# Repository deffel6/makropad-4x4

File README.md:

# Makropad 4 × 4

16 Tasten im 19,05-mm-Raster, Cherry MX, gesteuert von einem Pro Micro über
acht Lötpunkte. Platine **96,2 × 92,2 mm**, zwei Lagen, vollständig verdrahtet.

Entwurf, Fertigungsdaten und Firmware liegen hier zusammen. Die Platine ist
nicht von Hand gezeichnet, sondern wird aus einem Skript erzeugt — Rastermaß
und Tastenzahl sind dadurch eine Zahl im Kopf der Datei.

## Anschlüsse

Acht durchkontaktierte Lötpunkte in einer Reihe am oberen Rand, im
2,54-mm-Raster. Von links:

```
R3  R2  R1  R0  C0  C1  C2  C3
```

| Lötpunkt | QMK | Aufdruck am Pro Micro | Arduino |
|---|---|---|---|
| `R0` | `D4` | 4 | 4 |
| `R1` | `C6` | 5 | 5 |
| `R2` | `D7` | 6 | 6 |
| `R3` | `E6` | 7 | 7 |
| `C0` | `F4` | A3 | 21 |
| `C1` | `F5` | A2 | 20 |
| `C2` | `F6` | A1 | 19 |
| `C3` | `F7` | A0 | 18 |

Zeilen auf der linken Stiftleiste, Spalten auf der rechten, beide in der
unteren Hälfte des Moduls — so bleiben die Drähte kurz.

**Frei bleiben** `D0`/`D1` (I²C, für ein Display), `D2`/`D3` (seriell),
`B1`/`B2`/`B3` (SPI) sowie `B4`/`B5`/`B6`. Versorgung braucht die Platine
keine: Eine Tastenmatrix wird allein über die acht Signalleitungen abgefragt.

## Verdrahtung

```
Spalte ──── Schalter ──── Diode ──►── Zeile
                          Anode   Kathode
```

Die Diode verhindert Phantomtasten: Ohne sie schließen drei gleichzeitig
gedrückte Tasten einen Pfad über eine vierte, die gar nicht gedrückt ist.
Stromrichtung Spalte → Zeile, in QMK `COL2ROW`.

Spalten laufen senkrecht auf der Vorderseite, Zeilen waagerecht auf der
Rückseite. Weil jeder Lötpunkt auf der Achse seiner Bahn sitzt, kreuzt sich
nichts — die Platine kommt ohne eine einzige Durchkontaktierung aus.

| Vorderseite | Rückseite |
|---|---|
|  |  |

## Fertigen lassen

`hardware/keypad4x4-gerber.zip` bei einem Hersteller hochladen, nicht
entpacken. Voreinstellungen passen: zweilagig, 1,6 mm, HASL.

Geprüft ist die Platine mit dem Regelprüfer von KiCad 10:

```
Regelverstöße:        0
Unverbundene Stellen: 0
```

Dazu gegengelesen: Jedes der 40 Lötaugen hat eine durchkontaktierte Bohrung,
alle 52 Löcher ohne Kupfer sind vorhanden, 92 Bohrungen gesamt. Das Rastermaß
beträgt überall exakt 19,05 mm — auch von Zapfenloch zu Zapfenloch.

Wer die Dioden bestücken lassen will, findet in `bestueckung/` die Stückliste
und die Positionsdatei. Die 16 SOD-123 sitzen auf der **Unterseite**.

## Stückliste

| Menge | Teil | Hinweis |
|---|---|---|
| 16 | Cherry MX oder kompatibel | **PCB-Bauform mit fünf Beinen** |
| 16 | 1N4148W, SOD-123 | Rückseite, SMD |
| 1 | Pro Micro ATmega32U4 | oder steckkompatibler Ersatz |
| 1 | Stiftleiste 8-polig, 2,54 mm | |
| 4 | M2-Schraube mit Abstandshalter | Löcher Ø 2,2 mm |

Die Schalter brauchen die PCB-montierte Bauform mit zwei Kunststoffzapfen
neben den Kontakten — die Platine hat Löcher dafür. Die Plattenbauform ohne
Zapfen passt zwar hinein, sitzt aber lose.

## Firmware

Wer nicht selbst übersetzen will, nimmt die fertigen Dateien aus
[`firmware/fertig/`](firmware/fertig/) und flasht sie mit der
[QMK Toolbox](https://github.com/qmk/qmk_toolbox/releases) — dafür braucht es
weder QMK noch ein Terminal. Die Anleitung dazu liegt im selben Ordner.

> **Stand der fertigen Dateien:** Die beiden `.hex` stammen noch von der
> früheren Belegung (Zifferblock mit Ebenen-Taste unten rechts) und sind nicht
> neu übersetzt. Die Quellen in `firmware/keypad4x4/` haben bereits die neue
> Belegung mit 16 freien Tasten. Die Vial-Datei ist trotzdem brauchbar, weil
> sich dort jede Taste in der App umbelegen lässt. Die `default`-Datei hat die
> alte feste Belegung, bis sie mit `make keypad4x4:default` neu gebaut wird.

Selbst bauen: `firmware/keypad4x4/` nach `keyboards/` in QMK oder vial-qmk
kopieren, dann:

```
make keypad4x4:default          # feste Belegung
make keypad4x4:vial             # zur Laufzeit änderbar
```

Beide Fassungen sind übersetzt und geprüft:

| | Größe | Auslastung |
|---|---|---|
| default | 15.808 Bytes | 55 % |
| vial | 28.246 Bytes | 98 % |

Die Vial-Fassung passt nur knapp: Der Pro Micro hat nach Abzug des
Bootloaders 28.672 Bytes, und Vial bringt viel mit. In
`keymaps/vial/rules.mk` ist deshalb alles Entbehrliche abgeschaltet und die
Zahl der Ebenen auf drei begrenzt. **Für Erweiterungen ist kein Platz mehr.**
Wer mehr will, nimmt ein RP2040-Modul in Pro-Micro-Bauform — es passt auf
dieselben Lötpunkte und hat das Sechzehnfache an Speicher.

### ZMK mit ZMK Studio (nice!nano, kabellos)

Alternativ zum Pro Micro mit QMK: ein **nice!nano** auf denselben acht
Lötpunkten, Firmware in ZMK. Belegung wie oben, aber im Browser änderbar
(<https://zmk.studio>, Chrome oder Edge) und ohne Speicherproblem — der
nRF52840 hat 1 MB Flash. Die Dateien liegen im Wurzelverzeichnis
(`config/`, `boards/`, `build.yaml`), weil ZMKs GitHub-Build sie dort erwartet;
den Build startet ein Push, die `.uf2` liegt danach unter *Actions → Artifacts*.

| Lötpunkt | Pro-Micro-Pin |
|---|---|
| `R0` `R1` `R2` `R3` | 4 · 5 · 6 · 7 |
| `C0` `C1` `C2` `C3` | A3 (21) · A2 (20) · A1 (19) · A0 (18) |

Der Akku hängt direkt an `B+`/`B−` des nice!nano, die Platine hat keinen
Anschluss dafür. Studio ist nicht gesperrt (`CONFIG_ZMK_STUDIO_LOCKING=n` in
`config/keypad4x4.conf`), eine Entsperr-Taste braucht es also nicht und alle 16
Tasten bleiben frei. Dafür kann jeder Rechner, an dem das Pad per USB hängt,
die Belegung ändern. Wer das nicht will, setzt die Option auf `y` und legt
`&studio_unlock` auf eine Taste.

### Belegung

Alle 16 Tasten sind Programmtasten auf einer einzigen Ebene. Keine ist für einen
Ebenenwechsel oder die Studio-Entsperrung reserviert.

```
F13      F14      F15      F16
F17      F18      F19      F20
F21      F22      F23      F24
Meh+F13  Meh+F14  Meh+F15  Meh+F16
```

`F13` bis `F24` gibt es auf keiner gewöhnlichen Tastatur, und genau deshalb
sind sie brauchbar: Kein Programm belegt sie schon. Werkzeuge wie Hammerspoon
oder die Kurzbefehle-App können sie frei binden. Mehr als zwölf freie F-Tasten
kennt der USB-Standard nicht, deshalb liegen in der untersten Reihe `F13` bis
`F16` mit **Meh** (Strg + Umschalt + Alt) — in Hammerspoon `{"ctrl","alt","shift"}`.

Jede Taste lässt sich umbelegen: in ZMK mit Studio im Browser, in der
Vial-Fassung mit der Vial-App. Die frühere Belegung als Zifferblock mit
Ebenen-Taste ist damit ersetzt. Wer sie zurück will, legt sie in Studio oder
Vial wieder an und opfert dafür eine Taste als Ebenenschalter.

## Ändern

```bash
cd hardware && python3 generate_pcb.py && python3 preview.py
```

Oben in `generate_pcb.py` stehen `COLS`, `ROWS` und `PITCH`. Auf 5 × 4 oder
ein engeres Raster umzustellen ist eine Zeile — Platinengröße,
Bauteilpositionen und alle Leiterbahnen werden daraus gerechnet.

`preview.py` liest dabei die **erzeugte Platinendatei**, nicht die Absicht des
Generators. Ein Schreibfehler fällt dadurch im Bild auf, statt unbemerkt zu
bleiben. `gerber_render.py` geht noch einen Schritt weiter und zeichnet die
ausgelieferten Gerber- und Bohrdateien selbst — also das, was beim Hersteller
ankommt.

## Werkzeuge

KiCad 10 zum Ansehen und Bearbeiten, Python 3 für die Skripte, QMK oder
vial-qmk für die Firmware. Die Fußabdrücke stehen vollständig in der
Platinendatei, sie braucht also keine Bibliothek.

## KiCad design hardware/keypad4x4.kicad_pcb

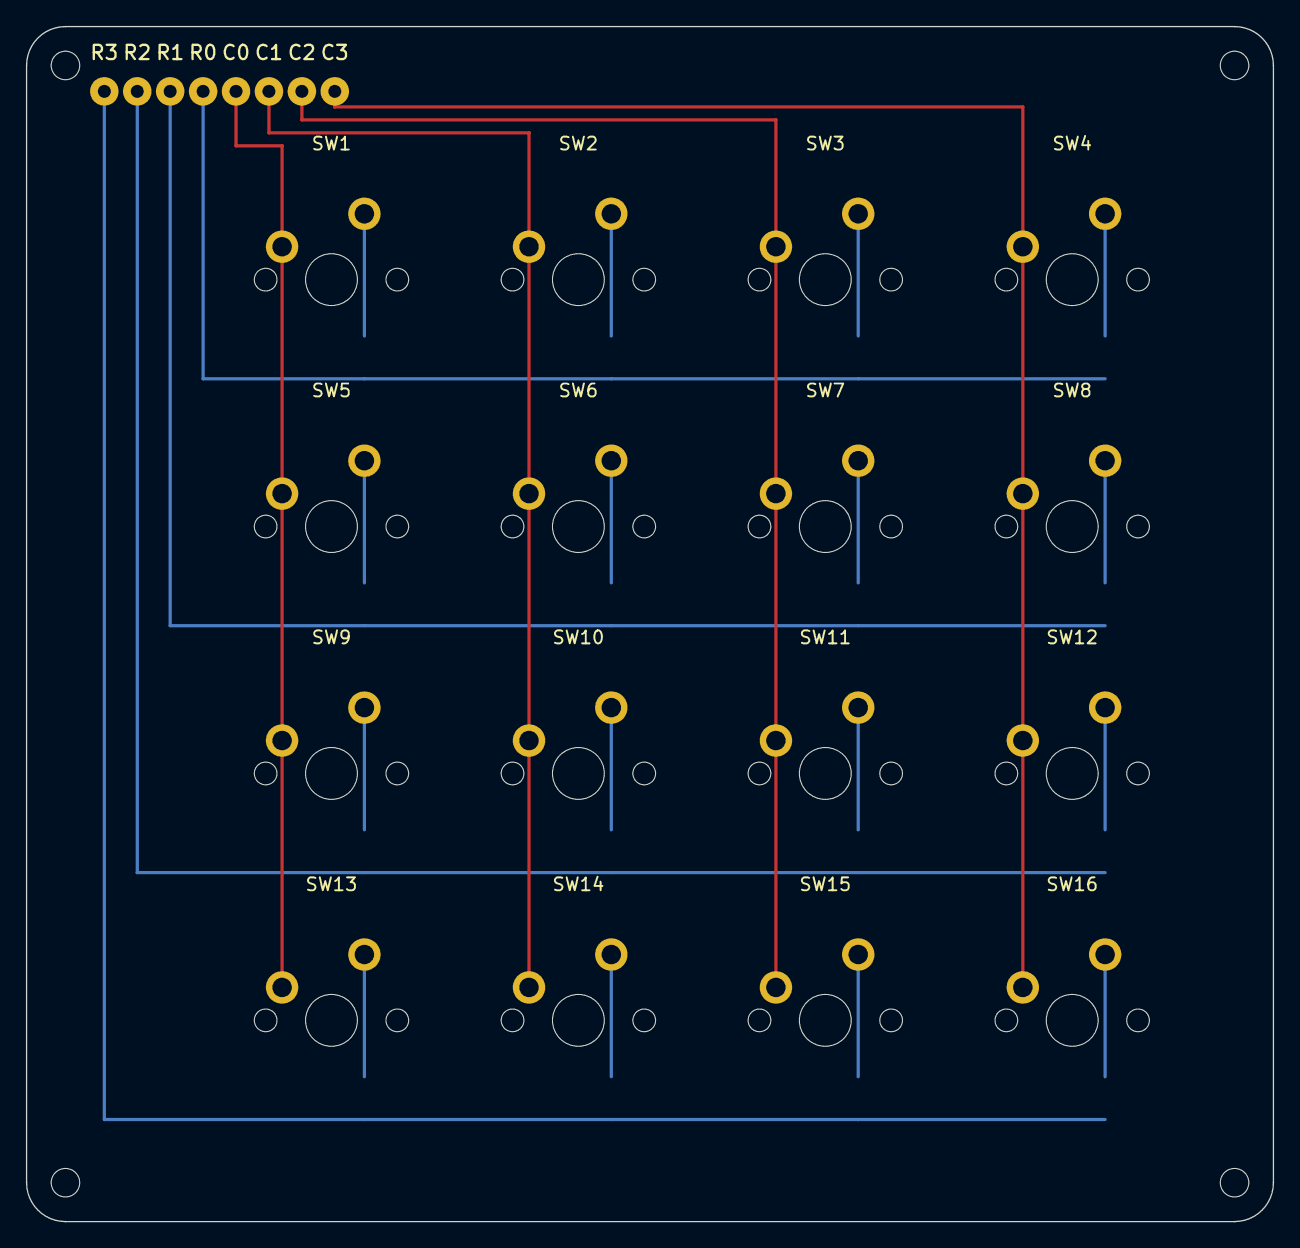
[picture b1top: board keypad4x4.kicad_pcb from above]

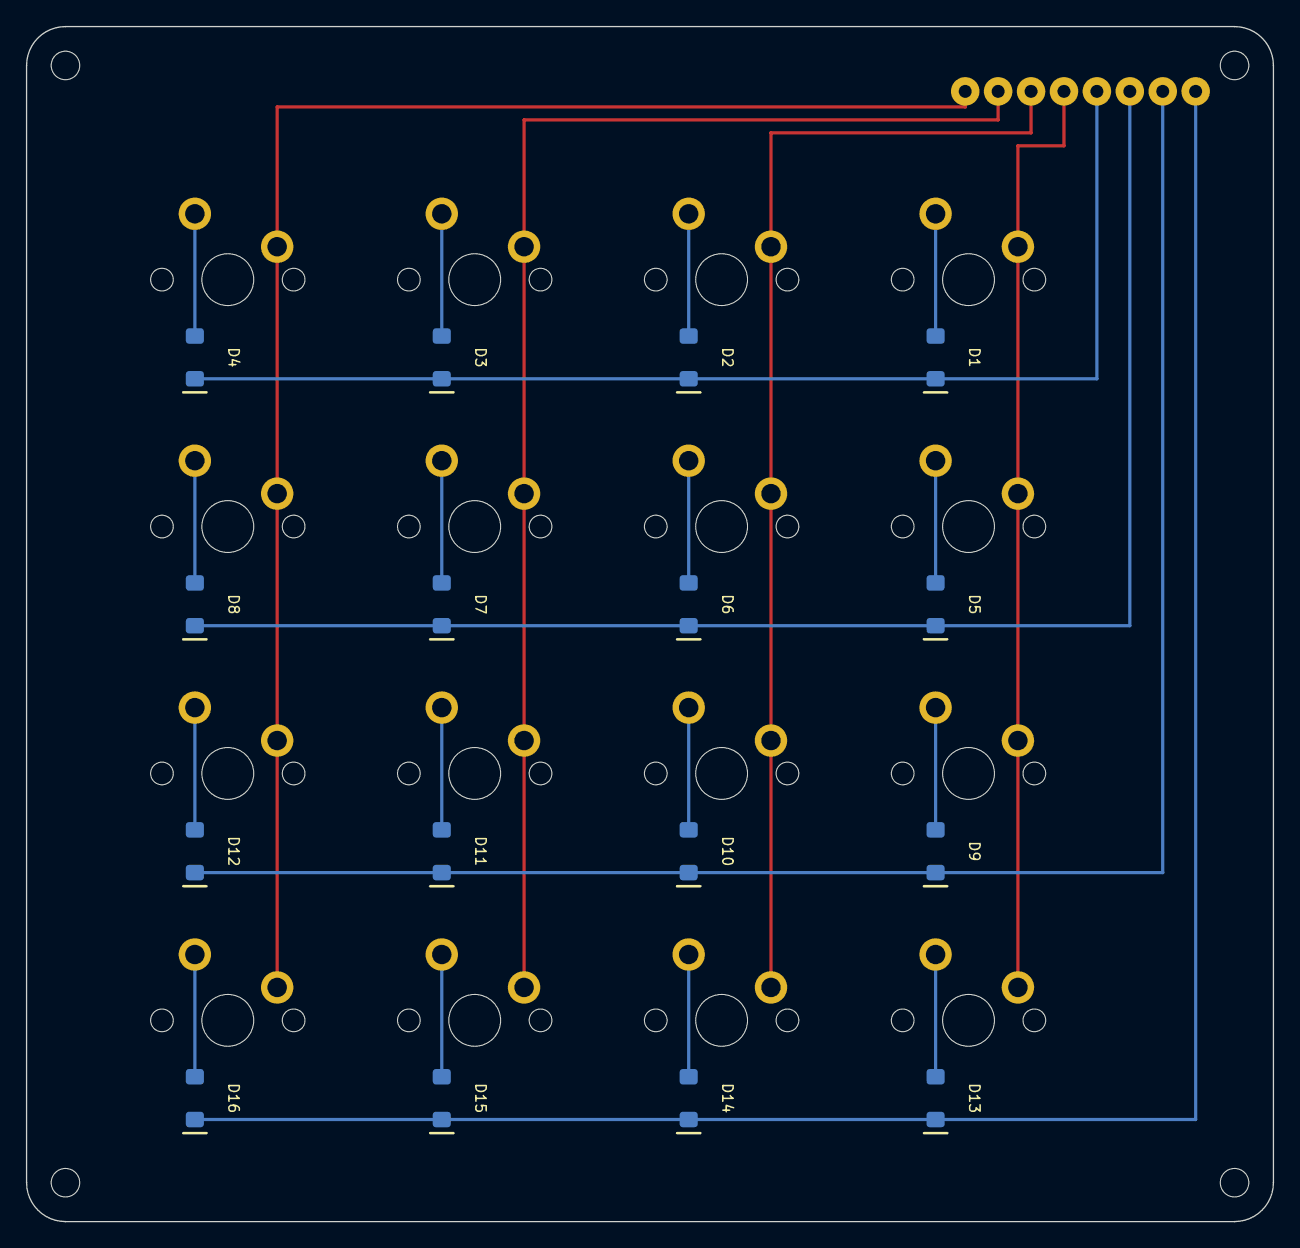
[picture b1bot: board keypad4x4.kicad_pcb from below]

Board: 2 copper layers, 96.2 x 92.2 mm, 40 parts (16 on the bottom side), 24 nets.

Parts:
D1, D2, D3, D4, D5, D6, D7, D8, D9, D10, D11, D12, D13, D14, D15, D16: 1N4148W; D_SOD-123
J1, J2, J3, J4, J5, J6, J7, J8: Pad
SW1, SW2, SW3, SW4, SW5, SW6, SW7, SW8, SW9, SW10, SW11, SW12, SW13, SW14, SW15, SW16: MX; MX_1u

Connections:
COL0: J5.1, SW1.1, SW5.1, SW9.1, SW13.1
COL1: J6.1, SW2.1, SW6.1, SW10.1, SW14.1
COL2: J7.1, SW3.1, SW7.1, SW11.1, SW15.1
COL3: J8.1, SW4.1, SW8.1, SW12.1, SW16.1
ROW0: D1.1, D2.1, D3.1, D4.1, J4.1
ROW1: D5.1, D6.1, D7.1, D8.1, J3.1
ROW2: D9.1, D10.1, D11.1, D12.1, J2.1
ROW3: D13.1, D14.1, D15.1, D16.1, J1.1
SW1_D: D1.2, SW1.2
SW2_D: D2.2, SW2.2
SW3_D: D3.2, SW3.2
SW4_D: D4.2, SW4.2
SW5_D: D5.2, SW5.2
SW6_D: D6.2, SW6.2
SW7_D: D7.2, SW7.2
SW8_D: D8.2, SW8.2
SW9_D: D9.2, SW9.2
SW10_D: D10.2, SW10.2
SW11_D: D11.2, SW11.2
SW12_D: D12.2, SW12.2
SW13_D: D13.2, SW13.2
SW14_D: D14.2, SW14.2
SW15_D: D15.2, SW15.2
SW16_D: D16.2, SW16.2
